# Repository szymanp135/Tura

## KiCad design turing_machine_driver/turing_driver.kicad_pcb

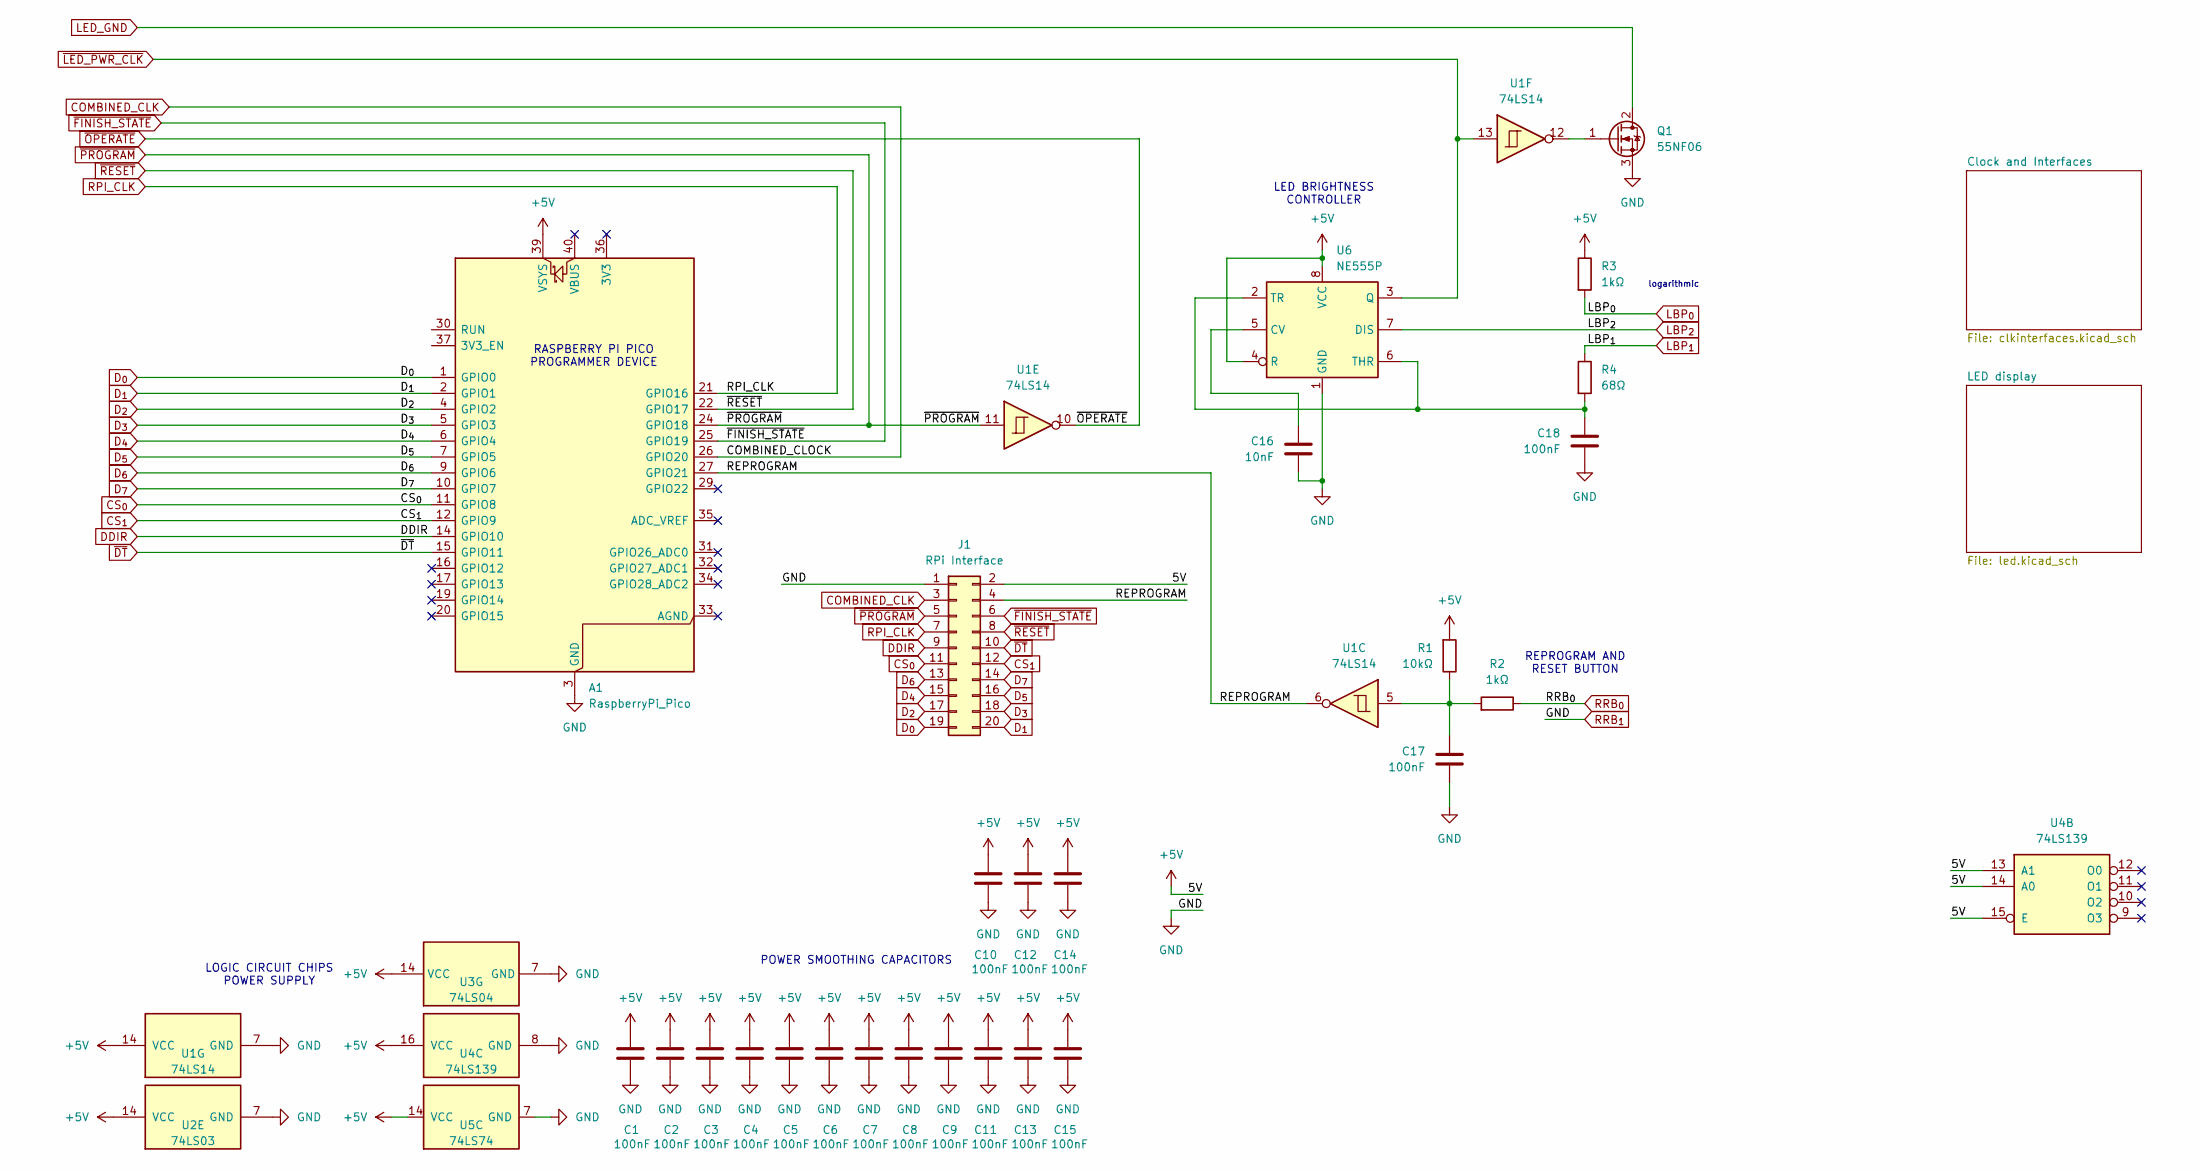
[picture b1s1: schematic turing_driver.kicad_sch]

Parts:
A1: RaspberryPi_Pico; RaspberryPi_Pico_Common_THT
C1, C2, C3, C4, C5, C6, C7, C8, C9, C10, C11, C12, C13, C14, C15, C17: 100nF; C_Disc_D3.8mm_W2.6mm_P2.50mm
C16: 10nF; C_Disc_D5.1mm_W3.2mm_P5.00mm
C18: 100nF; C_Disc_D5.1mm_W3.2mm_P5.00mm
J1: RPi Interface; IDC-Header_2x10_P2.54mm_Vertical
Q1: 55NF06; TO-220-3_Horizontal_TabDown
R1: 10kΩ; R_Axial_DIN0207_L6.3mm_D2.5mm_P10.16mm_Horizontal
R2, R3: 1kΩ; R_Axial_DIN0207_L6.3mm_D2.5mm_P10.16mm_Horizontal
R4: 68Ω; R_Axial_DIN0207_L6.3mm_D2.5mm_P10.16mm_Horizontal
U1: 74LS14; DIP-14_W7.62mm
U2: 74LS03; DIP-14_W7.62mm
U3: 74LS04; DIP-14_W7.62mm
U4: 74LS139; DIP-16_W7.62mm
U5: 74LS74; DIP-14_W7.62mm
U6: NE555P; DIP-8_W7.62mm

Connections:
/REPROGRAM: A1.27 (GPIO21), J1.4, U1.6
COMBINED_CLK: A1.26 (GPIO20), J1.3; also elsewhere on the board
CS_{0}: A1.11 (GPIO8), J1.11; also elsewhere on the board
CS_{1}: A1.12 (GPIO9), J1.12; also elsewhere on the board
DDIR: A1.14 (GPIO10), J1.9; also elsewhere on the board
D_{0}: A1.1 (GPIO0), J1.19; also elsewhere on the board
D_{1}: A1.2 (GPIO1), J1.20; also elsewhere on the board
D_{2}: A1.4 (GPIO2), J1.17; also elsewhere on the board
D_{3}: A1.5 (GPIO3), J1.18; also elsewhere on the board
D_{4}: A1.6 (GPIO4), J1.15; also elsewhere on the board
D_{5}: A1.7 (GPIO5), J1.16; also elsewhere on the board
D_{6}: A1.9 (GPIO6), J1.13; also elsewhere on the board
D_{7}: A1.10 (GPIO7), J1.14; also elsewhere on the board
LBP_{0}: R3.2; also elsewhere on the board
LBP_{1}: R4.1; also elsewhere on the board
LBP_{2}: U6.7 (DIS); also elsewhere on the board
LED_GND: Q1.2 (D); also elsewhere on the board
LPS_{0}: A1.39 (VSYS), C1.1, C2.1, C3.1, C4.1, C5.1, C6.1, C7.1, C8.1, C9.1, C10.1, C11.1, C12.1, C13.1, C14.1, C15.1, J1.2, R1.2, R3.1, U1.14 (VCC), U2.14 (VCC), U3.14 (VCC), U4.13 (A1), U4.14 (A0), U4.15 (E), U4.16 (VCC), U5.14 (VCC), U6.4 (R), U6.8 (VCC); also elsewhere on the board
unnamed: C17.1, R1.1, R2.2, U1.5
unnamed: Q1.1 (G), U1.12
unnamed: C16.1, U6.5 (CV)
unnamed: C18.1, R4.2, U6.2 (TR), U6.6 (THR)
RPI_CLK: A1.21 (GPIO16), J1.7; also elsewhere on the board
RRB_{0}: R2.1; also elsewhere on the board
RRB_{1}: A1.3 (GND), A1.8 (GND), A1.13 (GND), A1.18 (GND), A1.23 (GND), A1.28 (GND), A1.38 (GND), C1.2, C2.2, C3.2, C4.2, C5.2, C6.2, C7.2, C8.2, C9.2, C10.2, C11.2, C12.2, C13.2, C14.2, C15.2, C16.2, C17.2, C18.2, J1.1, Q1.3 (S), U1.7 (GND), U2.7 (GND), U3.7 (GND), U4.8 (GND), U5.7 (GND), U6.1 (GND); also elsewhere on the board
~DT: A1.15 (GPIO11), J1.10; also elsewhere on the board
~FINISH_STATE: A1.25 (GPIO19), J1.6; also elsewhere on the board
~LED_PWR_CLK: U1.13, U6.3 (Q); also elsewhere on the board
~OPERATE: U1.10; also elsewhere on the board
~PROGRAM: A1.24 (GPIO18), J1.5, U1.11; also elsewhere on the board
~RESET: A1.22 (GPIO17), J1.8; also elsewhere on the board

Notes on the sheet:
RASPBERRY PI PICO PROGRAMMER DEVICE
LOGIC CIRCUIT CHIPS POWER SUPPLY
REPROGRAM AND RESET BUTTON
POWER SMOOTHING CAPACITORS
logarithmic
LED BRIGHTNESS CONTROLLER

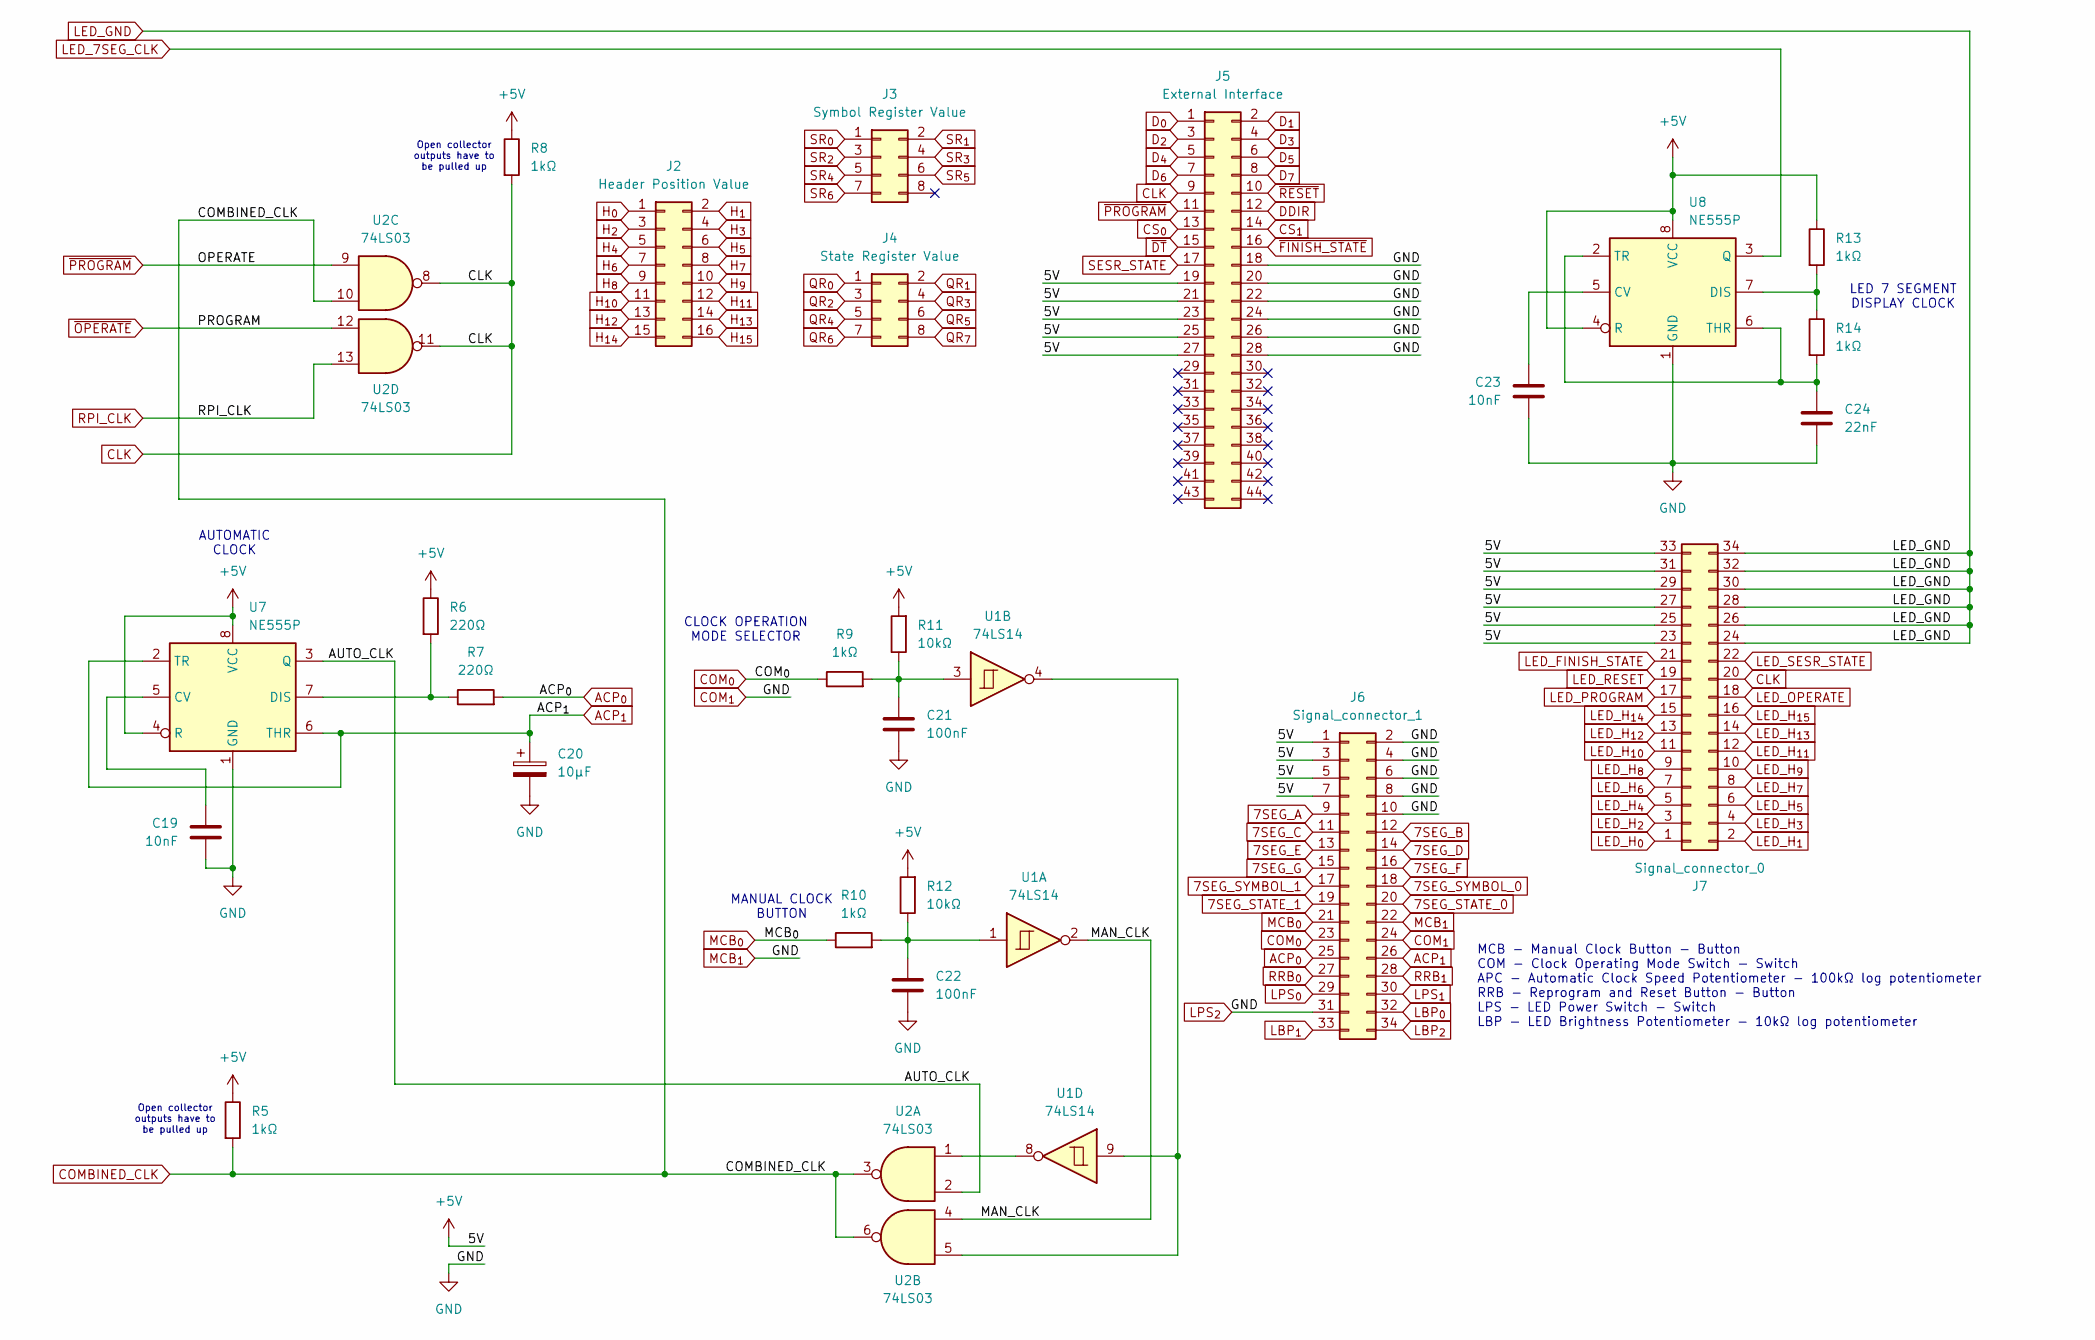
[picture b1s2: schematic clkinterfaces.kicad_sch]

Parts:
C19, C23: 10nF; C_Disc_D5.1mm_W3.2mm_P5.00mm
C20: 10µF; CP_Radial_D5.0mm_P2.00mm
C21, C22: 100nF; C_Disc_D3.8mm_W2.6mm_P2.50mm
C24: 22nF; C_Disc_D5.1mm_W3.2mm_P5.00mm
J2: Header Position Value; IDC-Header_2x08_P2.54mm_Vertical
J3: Symbol Register Value; IDC-Header_2x04_P2.54mm_Vertical
J4: State Register Value; IDC-Header_2x04_P2.54mm_Vertical
J5: External Interface; Connector_Edge_2x22pin_odd
J6: Signal_connector_1; Connector_Edge_2x17pin_odd
J7: Signal_connector_0; Connector_Edge_2x17pin_odd
R5, R8, R9, R10, R13, R14: 1kΩ; R_Axial_DIN0207_L6.3mm_D2.5mm_P10.16mm_Horizontal
R6, R7: 220Ω; R_Axial_DIN0207_L6.3mm_D2.5mm_P10.16mm_Horizontal
R11, R12: 10kΩ; R_Axial_DIN0207_L6.3mm_D2.5mm_P10.16mm_Horizontal
U1: 74LS14; DIP-14_W7.62mm
U2: 74LS03; DIP-14_W7.62mm
U7, U8: NE555P; DIP-8_W7.62mm

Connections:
7SEG_A: J6.9; also elsewhere on the board
7SEG_B: J6.12; also elsewhere on the board
7SEG_C: J6.11; also elsewhere on the board
7SEG_D: J6.14; also elsewhere on the board
7SEG_E: J6.13; also elsewhere on the board
7SEG_F: J6.16; also elsewhere on the board
7SEG_G: J6.15; also elsewhere on the board
7SEG_STATE_0: J6.20; also elsewhere on the board
7SEG_STATE_1: J6.19; also elsewhere on the board
7SEG_SYMBOL_0: J6.18; also elsewhere on the board
7SEG_SYMBOL_1: J6.17; also elsewhere on the board
/Clock and Interfaces/AUTO_CLK: U2.2, U7.3 (Q)
/Clock and Interfaces/MAN_CLK: U1.2, U2.4
ACP_{0}: J6.25, R7.2
ACP_{1}: C20.1, J6.26, U7.2 (TR), U7.6 (THR)
CLK: J5.9, J7.20, R8.2, U2.8, U2.11; also elsewhere on the board
COMBINED_CLK: R5.2, U2.3, U2.6, U2.10; also elsewhere on the board
COM_{0}: J6.23, R9.1
CS_{0}: J5.13; also elsewhere on the board
CS_{1}: J5.14; also elsewhere on the board
DDIR: J5.12; also elsewhere on the board
D_{0}: J5.1; also elsewhere on the board
D_{1}: J5.2; also elsewhere on the board
D_{2}: J5.3; also elsewhere on the board
D_{3}: J5.4; also elsewhere on the board
D_{4}: J5.5; also elsewhere on the board
D_{5}: J5.6; also elsewhere on the board
D_{6}: J5.7; also elsewhere on the board
D_{7}: J5.8; also elsewhere on the board
H_{0}: J2.1; also elsewhere on the board
H_{1}: J2.2; also elsewhere on the board
H_{2}: J2.3; also elsewhere on the board
H_{3}: J2.4; also elsewhere on the board
H_{4}: J2.5; also elsewhere on the board
H_{5}: J2.6; also elsewhere on the board
H_{6}: J2.7; also elsewhere on the board
H_{7}: J2.8; also elsewhere on the board
H_{8}: J2.9; also elsewhere on the board
H_{9}: J2.10; also elsewhere on the board
H_{10}: J2.11; also elsewhere on the board
H_{11}: J2.12; also elsewhere on the board
H_{12}: J2.13; also elsewhere on the board
H_{13}: J2.14; also elsewhere on the board
H_{14}: J2.15; also elsewhere on the board
H_{15}: J2.16; also elsewhere on the board
LBP_{0}: J6.32; also elsewhere on the board
LBP_{1}: J6.33; also elsewhere on the board
LBP_{2}: J6.34; also elsewhere on the board
LED_7SEG_CLK: U8.3 (Q); also elsewhere on the board
LED_FINISH_STATE: J7.21; also elsewhere on the board
LED_GND: J7.24, J7.26, J7.28, J7.30, J7.32, J7.34; also elsewhere on the board
LED_H_{0}: J7.1; also elsewhere on the board
LED_H_{1}: J7.2; also elsewhere on the board
LED_H_{2}: J7.3; also elsewhere on the board
LED_H_{3}: J7.4; also elsewhere on the board
LED_H_{4}: J7.5; also elsewhere on the board
LED_H_{5}: J7.6; also elsewhere on the board
LED_H_{6}: J7.7; also elsewhere on the board
LED_H_{7}: J7.8; also elsewhere on the board
LED_H_{8}: J7.9; also elsewhere on the board
LED_H_{9}: J7.10; also elsewhere on the board
LED_H_{10}: J7.11; also elsewhere on the board
LED_H_{11}: J7.12; also elsewhere on the board
LED_H_{12}: J7.13; also elsewhere on the board
LED_H_{13}: J7.14; also elsewhere on the board
LED_H_{14}: J7.15; also elsewhere on the board
LED_H_{15}: J7.16; also elsewhere on the board
LED_OPERATE: J7.18; also elsewhere on the board
LED_PROGRAM: J7.17; also elsewhere on the board
LED_RESET: J7.19; also elsewhere on the board
LED_SESR_STATE: J7.22; also elsewhere on the board
LPS_{0}: J5.19, J5.21, J5.23, J5.25, J5.27, J6.1, J6.3, J6.5, J6.7, J6.29, J7.23, J7.25, J7.27, J7.29, J7.31, J7.33, R5.1, R6.1, R8.1, R11.2, R12.2, R13.1, U7.4 (R), U7.8 (VCC), U8.4 (R), U8.8 (VCC); also elsewhere on the board
LPS_{1}: J6.30; also elsewhere on the board
MCB_{0}: J6.21, R10.1
unnamed: C21.1, R9.2, R11.1, U1.3
unnamed: C22.1, R10.2, R12.1, U1.1
unnamed: U1.4, U1.9, U2.5
unnamed: U1.8, U2.1
unnamed: C19.1, U7.5 (CV)
unnamed: R6.2, R7.1, U7.7 (DIS)
unnamed: C23.1, U8.5 (CV)
unnamed: R13.2, R14.1, U8.7 (DIS)
unnamed: C24.1, R14.2, U8.2 (TR), U8.6 (THR)
QR_{0}: J4.1; also elsewhere on the board
QR_{1}: J4.2; also elsewhere on the board
QR_{2}: J4.3; also elsewhere on the board
QR_{3}: J4.4; also elsewhere on the board
QR_{4}: J4.5; also elsewhere on the board
QR_{5}: J4.6; also elsewhere on the board
QR_{6}: J4.7; also elsewhere on the board
QR_{7}: J4.8; also elsewhere on the board
RPI_CLK: U2.13; also elsewhere on the board
RRB_{0}: J6.27; also elsewhere on the board
RRB_{1}: C19.2, C20.2, C21.2, C22.2, C23.2, C24.2, J5.18, J5.20, J5.22, J5.24, J5.26, J5.28, J6.2, J6.4, J6.6, J6.8, J6.10, J6.22, J6.24, J6.28, J6.31, U7.1 (GND), U8.1 (GND); also elsewhere on the board
SESR_STATE: J5.17; also elsewhere on the board
SR_{0}: J3.1; also elsewhere on the board
SR_{1}: J3.2; also elsewhere on the board
SR_{2}: J3.3; also elsewhere on the board
SR_{3}: J3.4; also elsewhere on the board
SR_{4}: J3.5; also elsewhere on the board
SR_{5}: J3.6; also elsewhere on the board
SR_{6}: J3.7; also elsewhere on the board
~DT: J5.15; also elsewhere on the board
~FINISH_STATE: J5.16; also elsewhere on the board
~OPERATE: U2.12; also elsewhere on the board
~PROGRAM: J5.11, U2.9; also elsewhere on the board
~RESET: J5.10; also elsewhere on the board

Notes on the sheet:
AUTOMATIC CLOCK
Open collector outputs have to be pulled up
LED 7 SEGMENT DISPLAY CLOCK
MCB - Manual Clock Button - Button COM - Clock Operating Mode Switch - Switch APC - Automatic Clock Speed Potentiometer - 100kΩ log potentiometer RRB - Reprogram and Reset Button - Button LPS - LED Power Switch - Switch LBP - LED Brightness Potentiometer - 10kΩ log potentiometer
MANUAL CLOCK BUTTON
CLOCK OPERATION MODE SELECTOR

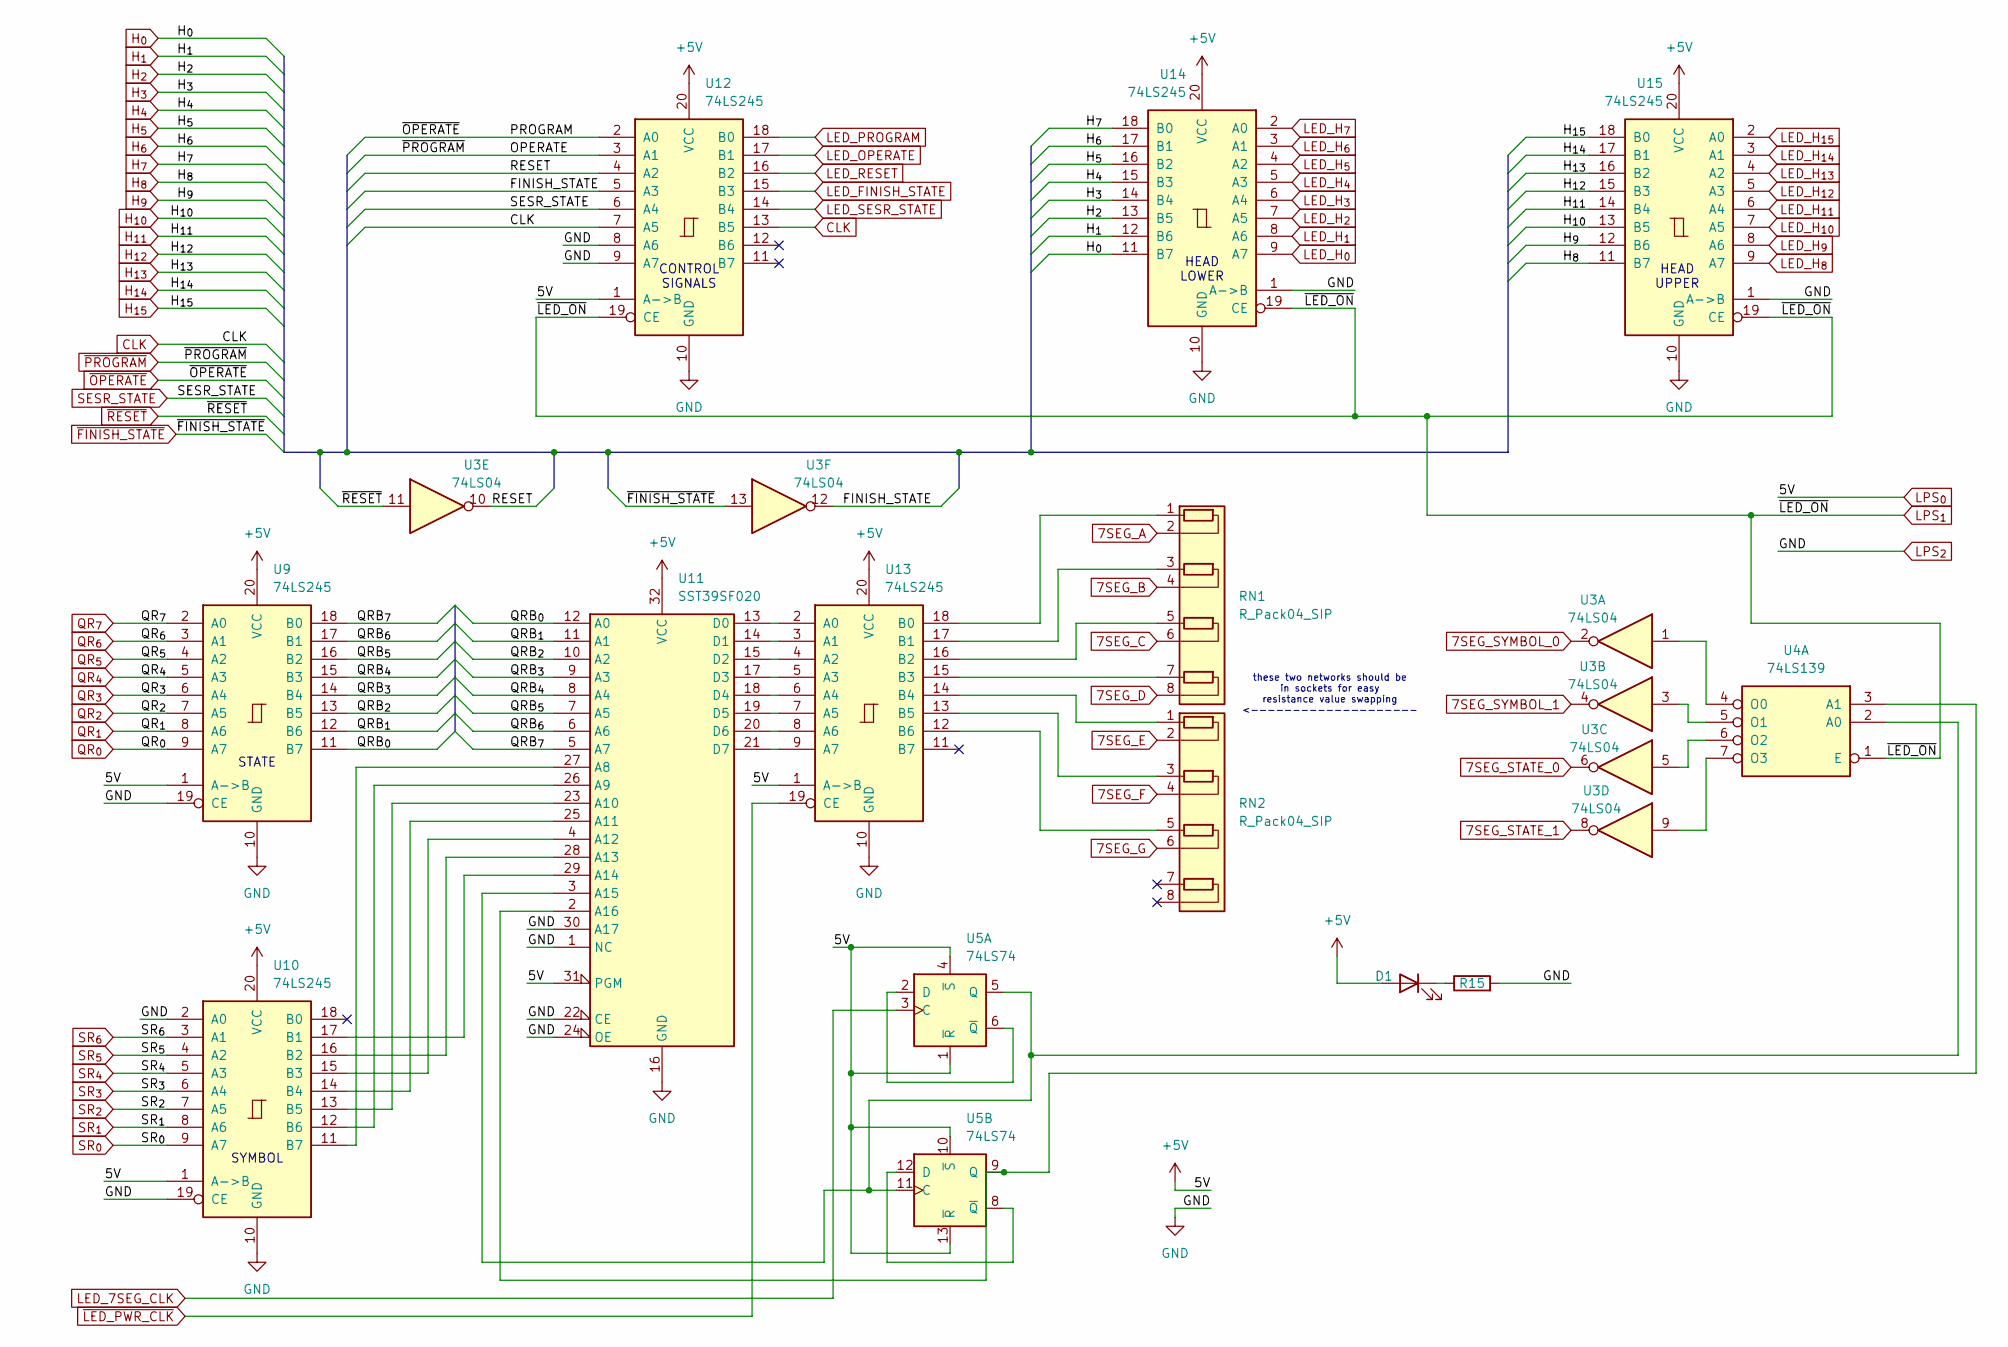
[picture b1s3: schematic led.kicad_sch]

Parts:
D1: LED_POWER_R; LED_D5.0mm
R15: 330Ω; R_Axial_DIN0207_L6.3mm_D2.5mm_P10.16mm_Horizontal
RN1, RN2: R_Pack04_SIP; R_Array_SIP8
U3: 74LS04; DIP-14_W7.62mm
U4: 74LS139; DIP-16_W7.62mm
U5: 74LS74; DIP-14_W7.62mm
U9, U10, U12, U13, U14, U15: 74LS245; DIP-20_W7.62mm
U11: SST39SF020; DIP-32_W15.24mm

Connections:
7SEG_A: RN1.2 (R1.2); also elsewhere on the board
7SEG_B: RN1.4 (R2.2); also elsewhere on the board
7SEG_C: RN1.6 (R3.2); also elsewhere on the board
7SEG_D: RN1.8 (R4.2); also elsewhere on the board
7SEG_E: RN2.2 (R1.2); also elsewhere on the board
7SEG_F: RN2.4 (R2.2); also elsewhere on the board
7SEG_G: RN2.6 (R3.2); also elsewhere on the board
7SEG_STATE_0: U3.6; also elsewhere on the board
7SEG_STATE_1: U3.8; also elsewhere on the board
7SEG_SYMBOL_0: U3.2; also elsewhere on the board
7SEG_SYMBOL_1: U3.4; also elsewhere on the board
/LED display/FINISH_STATE: U3.12, U12.5 (A3)
/LED display/QRB_{0}: U9.11 (B7), U11.12 (A0)
/LED display/QRB_{1}: U9.12 (B6), U11.11 (A1)
/LED display/QRB_{2}: U9.13 (B5), U11.10 (A2)
/LED display/QRB_{3}: U9.14 (B4), U11.9 (A3)
/LED display/QRB_{4}: U9.15 (B3), U11.8 (A4)
/LED display/QRB_{5}: U9.16 (B2), U11.7 (A5)
/LED display/QRB_{6}: U9.17 (B1), U11.6 (A6)
/LED display/QRB_{7}: U9.18 (B0), U11.5 (A7)
/LED display/RESET: U3.10, U12.4 (A2)
CLK: U12.7 (A5), U12.13 (B5); also elsewhere on the board
H_{0}: U14.11 (B7); also elsewhere on the board
H_{1}: U14.12 (B6); also elsewhere on the board
H_{2}: U14.13 (B5); also elsewhere on the board
H_{3}: U14.14 (B4); also elsewhere on the board
H_{4}: U14.15 (B3); also elsewhere on the board
H_{5}: U14.16 (B2); also elsewhere on the board
H_{6}: U14.17 (B1); also elsewhere on the board
H_{7}: U14.18 (B0); also elsewhere on the board
H_{8}: U15.11 (B7); also elsewhere on the board
H_{9}: U15.12 (B6); also elsewhere on the board
H_{10}: U15.13 (B5); also elsewhere on the board
H_{11}: U15.14 (B4); also elsewhere on the board
H_{12}: U15.15 (B3); also elsewhere on the board
H_{13}: U15.16 (B2); also elsewhere on the board
H_{14}: U15.17 (B1); also elsewhere on the board
H_{15}: U15.18 (B0); also elsewhere on the board
LED_7SEG_CLK: U5.3 (C); also elsewhere on the board
LED_FINISH_STATE: U12.15 (B3); also elsewhere on the board
LED_H_{0}: U14.9 (A7); also elsewhere on the board
LED_H_{1}: U14.8 (A6); also elsewhere on the board
LED_H_{2}: U14.7 (A5); also elsewhere on the board
LED_H_{3}: U14.6 (A4); also elsewhere on the board
LED_H_{4}: U14.5 (A3); also elsewhere on the board
LED_H_{5}: U14.4 (A2); also elsewhere on the board
LED_H_{6}: U14.3 (A1); also elsewhere on the board
LED_H_{7}: U14.2 (A0); also elsewhere on the board
LED_H_{8}: U15.9 (A7); also elsewhere on the board
LED_H_{9}: U15.8 (A6); also elsewhere on the board
LED_H_{10}: U15.7 (A5); also elsewhere on the board
LED_H_{11}: U15.6 (A4); also elsewhere on the board
LED_H_{12}: U15.5 (A3); also elsewhere on the board
LED_H_{13}: U15.4 (A2); also elsewhere on the board
LED_H_{14}: U15.3 (A1); also elsewhere on the board
LED_H_{15}: U15.2 (A0); also elsewhere on the board
LED_OPERATE: U12.17 (B1); also elsewhere on the board
LED_PROGRAM: U12.18 (B0); also elsewhere on the board
LED_RESET: U12.16 (B2); also elsewhere on the board
LED_SESR_STATE: U12.14 (B4); also elsewhere on the board
LPS_{0}: D1.2 (A), U5.1 (~R), U5.4 (~S), U5.10 (~S), U5.13 (~R), U9.1 (A->B), U9.20 (VCC), U10.1 (A->B), U10.20 (VCC), U11.31 (PGM), U11.32 (VCC), U12.1 (A->B), U12.20 (VCC), U13.1 (A->B), U13.20 (VCC), U14.20 (VCC), U15.20 (VCC); also elsewhere on the board
LPS_{1}: U4.1 (E), U12.19 (CE), U14.19 (CE), U15.19 (CE); also elsewhere on the board
unnamed: D1.1 (K), R15.1
unnamed: RN1.1 (R1.1), U13.18 (B0)
unnamed: RN1.3 (R2.1), U13.17 (B1)
unnamed: RN1.5 (R3.1), U13.16 (B2)
unnamed: RN1.7 (R4.1), U13.15 (B3)
unnamed: RN2.1 (R1.1), U13.14 (B4)
unnamed: RN2.3 (R2.1), U13.13 (B5)
unnamed: RN2.5 (R3.1), U13.12 (B6)
unnamed: U3.1, U4.4 (O0)
unnamed: U3.3, U4.5 (O1)
unnamed: U3.5, U4.6 (O2)
unnamed: U3.9, U4.7 (O3)
unnamed: U5.2 (D), U5.6 (~Q)
unnamed: U5.8 (~Q), U5.12 (D)
unnamed: U10.17 (B1), U11.29 (A14)
unnamed: U10.16 (B2), U11.28 (A13)
unnamed: U10.15 (B3), U11.4 (A12)
unnamed: U10.14 (B4), U11.25 (A11)
unnamed: U10.13 (B5), U11.23 (A10)
unnamed: U10.12 (B6), U11.26 (A9)
unnamed: U10.11 (B7), U11.27 (A8)
unnamed: U4.2 (A0), U5.5 (Q), U5.11 (C), U11.3 (A15)
unnamed: U4.3 (A1), U5.9 (Q), U11.2 (A16)
unnamed: U11.13 (D0), U13.2 (A0)
unnamed: U11.14 (D1), U13.3 (A1)
unnamed: U11.15 (D2), U13.4 (A2)
unnamed: U11.17 (D3), U13.5 (A3)
unnamed: U11.18 (D4), U13.6 (A4)
unnamed: U11.19 (D5), U13.7 (A5)
unnamed: U11.20 (D6), U13.8 (A6)
unnamed: U11.21 (D7), U13.9 (A7)
QR_{0}: U9.9 (A7); also elsewhere on the board
QR_{1}: U9.8 (A6); also elsewhere on the board
QR_{2}: U9.7 (A5); also elsewhere on the board
QR_{3}: U9.6 (A4); also elsewhere on the board
QR_{4}: U9.5 (A3); also elsewhere on the board
QR_{5}: U9.4 (A2); also elsewhere on the board
QR_{6}: U9.3 (A1); also elsewhere on the board
QR_{7}: U9.2 (A0); also elsewhere on the board
RRB_{1}: R15.2, U9.10 (GND), U9.19 (CE), U10.2 (A0), U10.10 (GND), U10.19 (CE), U11.1 (NC), U11.16 (GND), U11.22 (CE), U11.24 (OE), U11.30 (A17), U12.8 (A6), U12.9 (A7), U12.10 (GND), U13.10 (GND), U14.1 (A->B), U14.10 (GND), U15.1 (A->B), U15.10 (GND); also elsewhere on the board
SESR_STATE: U12.6 (A4); also elsewhere on the board
SR_{0}: U10.9 (A7); also elsewhere on the board
SR_{1}: U10.8 (A6); also elsewhere on the board
SR_{2}: U10.7 (A5); also elsewhere on the board
SR_{3}: U10.6 (A4); also elsewhere on the board
SR_{4}: U10.5 (A3); also elsewhere on the board
SR_{5}: U10.4 (A2); also elsewhere on the board
SR_{6}: U10.3 (A1); also elsewhere on the board
~FINISH_STATE: U3.13; also elsewhere on the board
~LED_PWR_CLK: U13.19 (CE); also elsewhere on the board
~OPERATE: U12.2 (A0); also elsewhere on the board
~PROGRAM: U12.3 (A1); also elsewhere on the board
~RESET: U3.11; also elsewhere on the board

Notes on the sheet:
HEAD UPPER
SYMBOL
CONTROL SIGNALS
these two networks should be in sockets for easy resistance value swapping <--------------------
HEAD LOWER
STATE

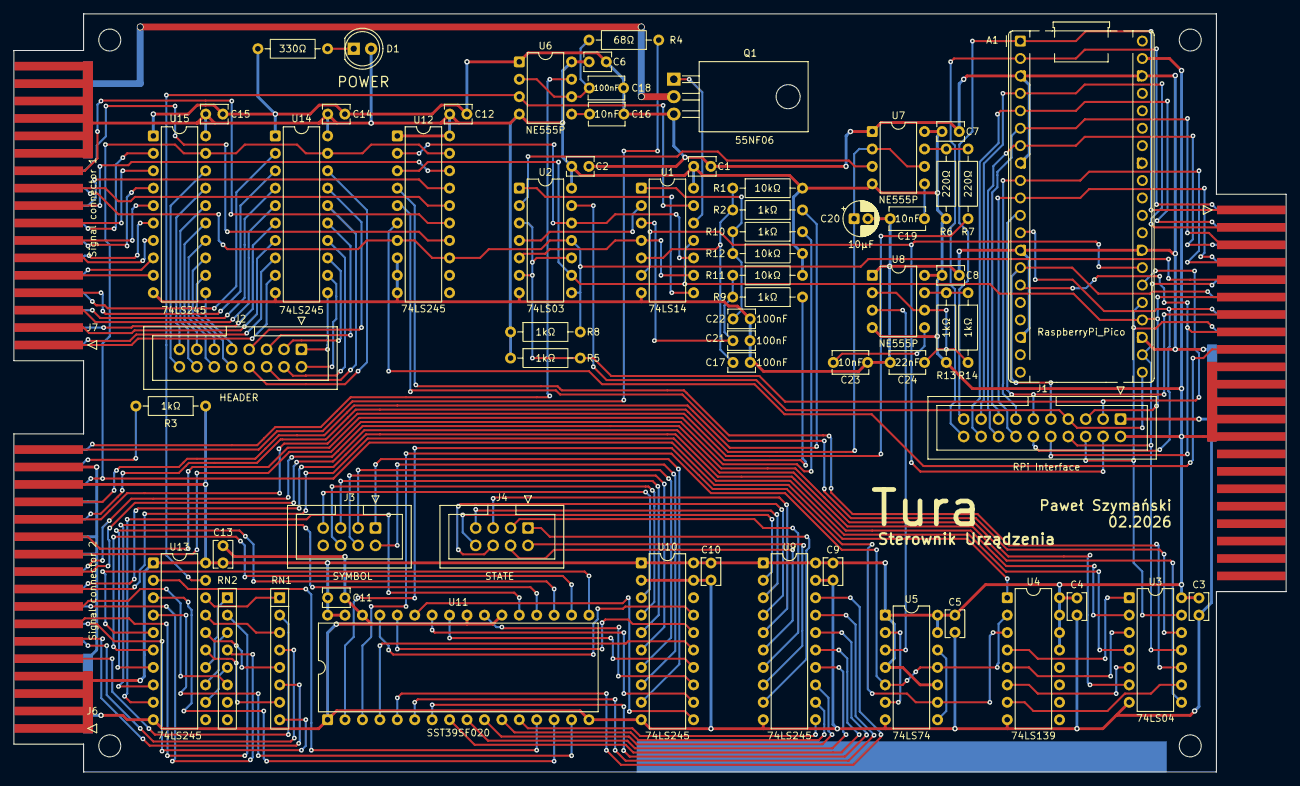
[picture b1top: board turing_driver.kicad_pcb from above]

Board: 2 copper layers, 185.4 x 110.5 mm, 66 parts (0 on the bottom side), 154 nets.

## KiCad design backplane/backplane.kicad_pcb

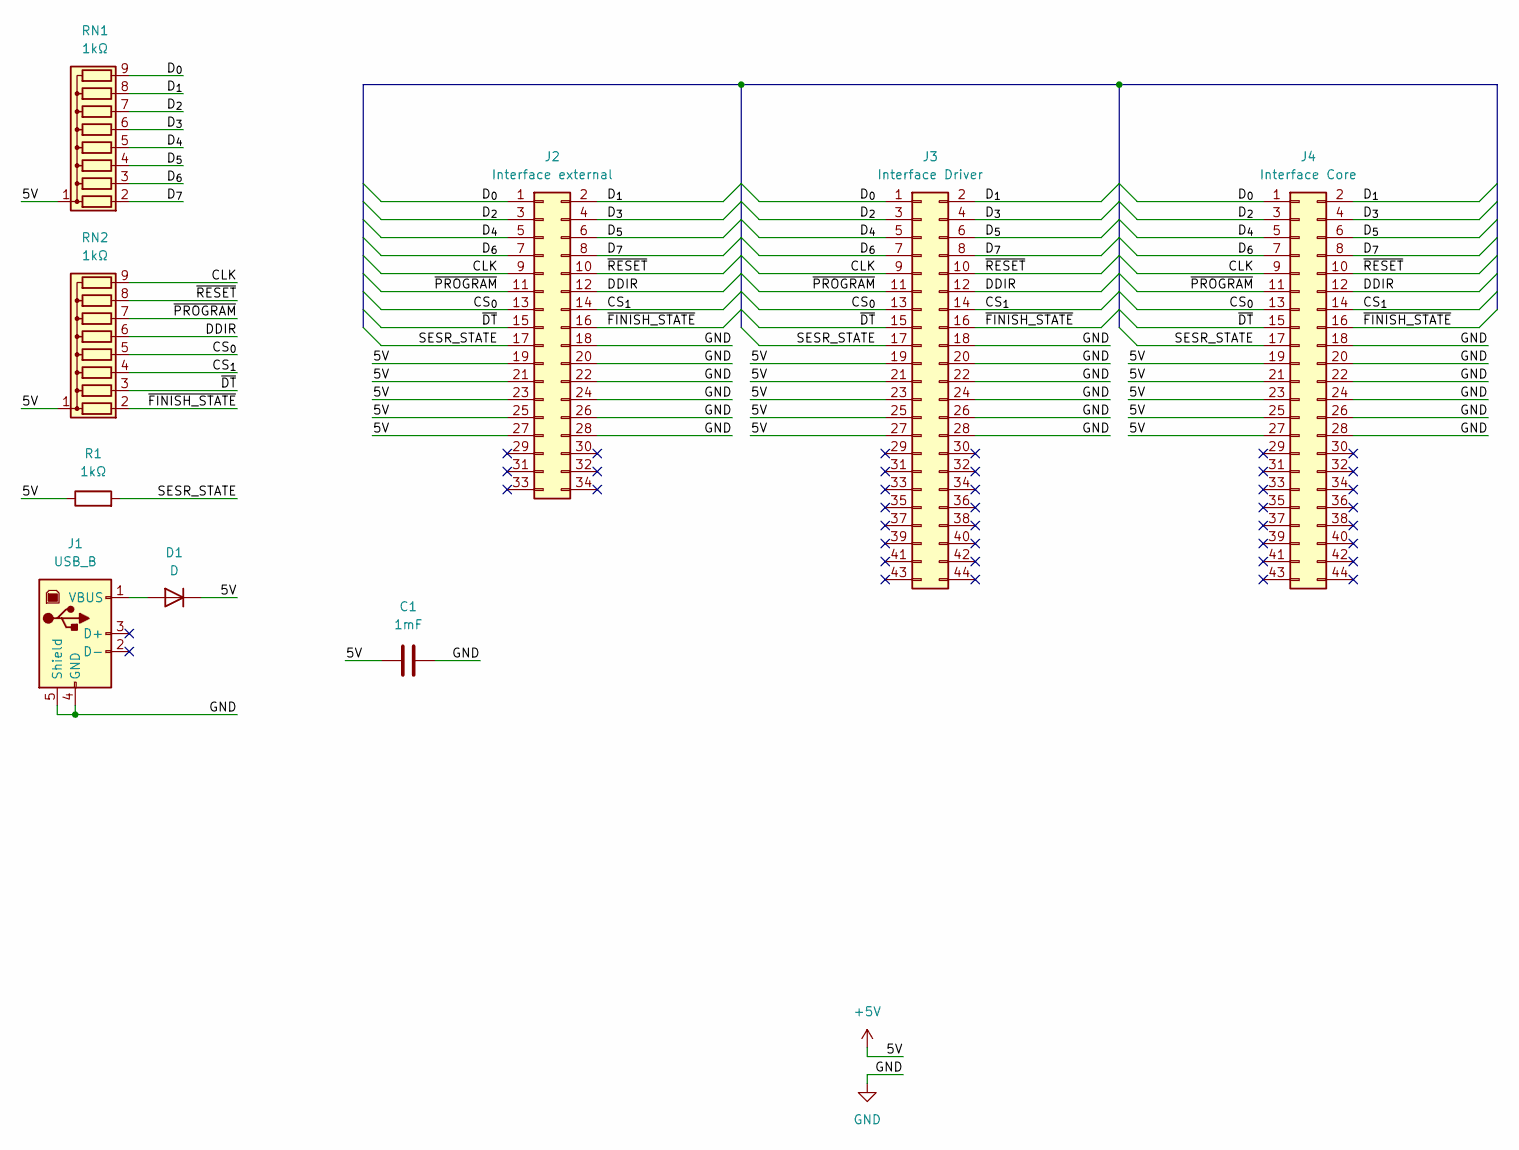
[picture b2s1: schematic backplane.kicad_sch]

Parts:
C1: 1mF; C_Radial_D12.5mm_H20.0mm_P5.00mm
D1: D; D_DO-35_SOD27_P10.16mm_Horizontal
J1: USB_B; USB_B_OST_USB-B1HSxx_Horizontal
J2: Interface external; IDC-Header_2x17_P2.54mm_Vertical
J3: Interface Driver; Connector_IDC_Edge_2x22pin_odd
J4: Interface Core; Connector_IDC_Edge_2x22pin_odd
R1: 1kΩ
RN1, RN2: 1kΩ; R_Array_SIP9

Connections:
+5V: C1.1, D1.1 (K), J2.19, J2.21, J2.23, J2.25, J2.27, J3.19, J3.21, J3.23, J3.25, J3.27, J4.19, J4.21, J4.23, J4.25, J4.27, R1.1, RN1.1 (common), RN2.1 (common)
/CLK: J2.9, J3.9, J4.9, RN2.9 (R8)
/CS_{0}: J2.13, J3.13, J4.13, RN2.5 (R4)
/CS_{1}: J2.14, J3.14, J4.14, RN2.4 (R3)
/DDIR: J2.12, J3.12, J4.12, RN2.6 (R5)
/D_{0}: J2.1, J3.1, J4.1, RN1.9 (R8)
/D_{1}: J2.2, J3.2, J4.2, RN1.8 (R7)
/D_{2}: J2.3, J3.3, J4.3, RN1.7 (R6)
/D_{3}: J2.4, J3.4, J4.4, RN1.6 (R5)
/D_{4}: J2.5, J3.5, J4.5, RN1.5 (R4)
/D_{5}: J2.6, J3.6, J4.6, RN1.4 (R3)
/D_{6}: J2.7, J3.7, J4.7, RN1.3 (R2)
/D_{7}: J2.8, J3.8, J4.8, RN1.2 (R1)
/SESR_STATE: J2.17, J3.17, J4.17, R1.2
/~DT: J2.15, J3.15, J4.15, RN2.3 (R2)
/~FINISH_STATE: J2.16, J3.16, J4.16, RN2.2 (R1)
/~PROGRAM: J2.11, J3.11, J4.11, RN2.7 (R6)
/~RESET: J2.10, J3.10, J4.10, RN2.8 (R7)
GND: C1.2, J1.4 (GND), J1.5 (Shield), J2.18, J2.20, J2.22, J2.24, J2.26, J2.28, J3.18, J3.20, J3.22, J3.24, J3.26, J3.28, J4.18, J4.20, J4.22, J4.24, J4.26, J4.28
unnamed: D1.2 (A), J1.1 (VBUS)

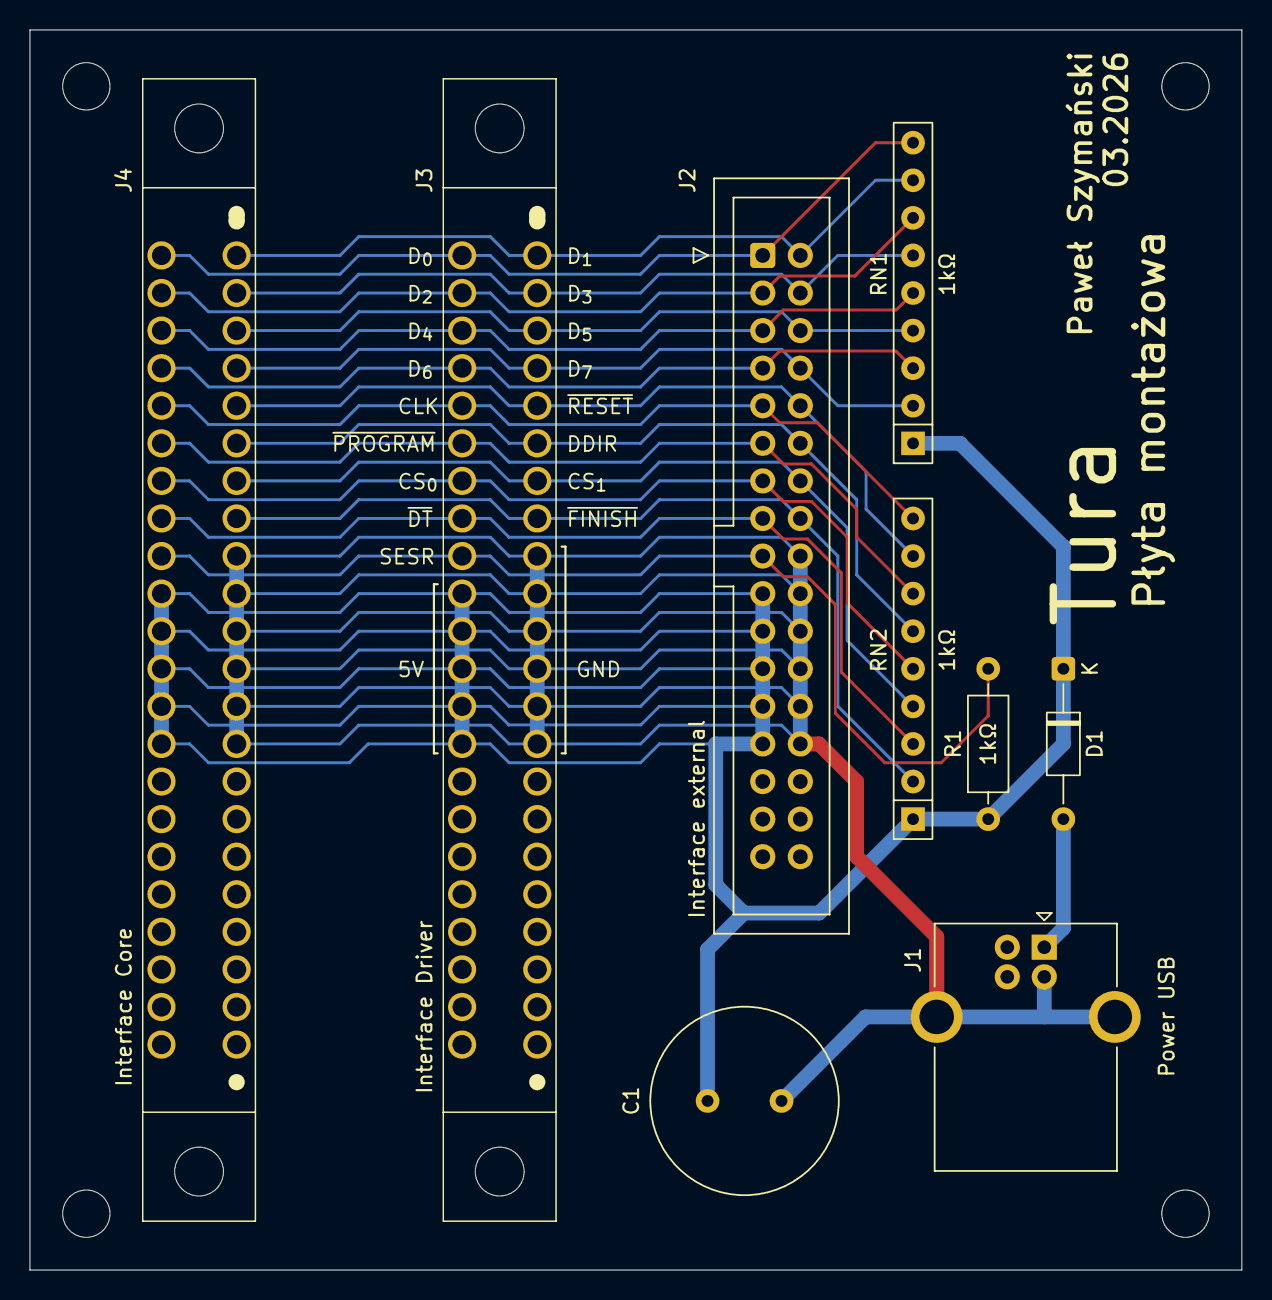
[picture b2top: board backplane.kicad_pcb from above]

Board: 2 copper layers, 81.9 x 83.8 mm, 9 parts (0 on the bottom side), 20 nets.
